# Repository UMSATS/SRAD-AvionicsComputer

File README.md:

# SRAD_V2

This repository contains the schematic, PCB, and supporting design files for the Student Researched and Designed (SRAD) rocket avionics computer.

## Project Structure

- **SRAD_V2.kicad_pro** — Main KiCad project file
- **SRAD_V2.kicad_sch** — Schematic file containing the full circuit design.
- **SRAD_V2.kicad_pcb** — PCB layout file for board routing and placement.
- **SRAD_V2-backups/** — Automatically generated backup files created by KiCad.
- **Custom E-cad Models/** — Custom or project-specific component symbols, footprints and 3D models used in the PCB design.

---

## System Overview

The schematic is organized into blocks for clarity:

- **Power Delivery System (PDS)**  
  Handles voltage regulation and distribution. Goal is to provide stable power to all avionics subsystems.

- **E-match Firing Circuit (EMFC)**  
  Provides quick burst of high current to e-matches via four separate channels. It also includes short circuit protection and various other safety features.

- **MCU (Microcontroller Unit)**  
  Central controller that interfaces with all sensors and peripherals. Will run the flight software and handle communication.

- **IMU for Sensing Motion and Temperature** -> LSM6DSV80XTR

- **Magnetometer** -> MMC5983MA

- **Barometer** -> MS5607-02BA

- **GPS** -> MAX-M10S

- **Data Storage** -> AT25SFQ64

---

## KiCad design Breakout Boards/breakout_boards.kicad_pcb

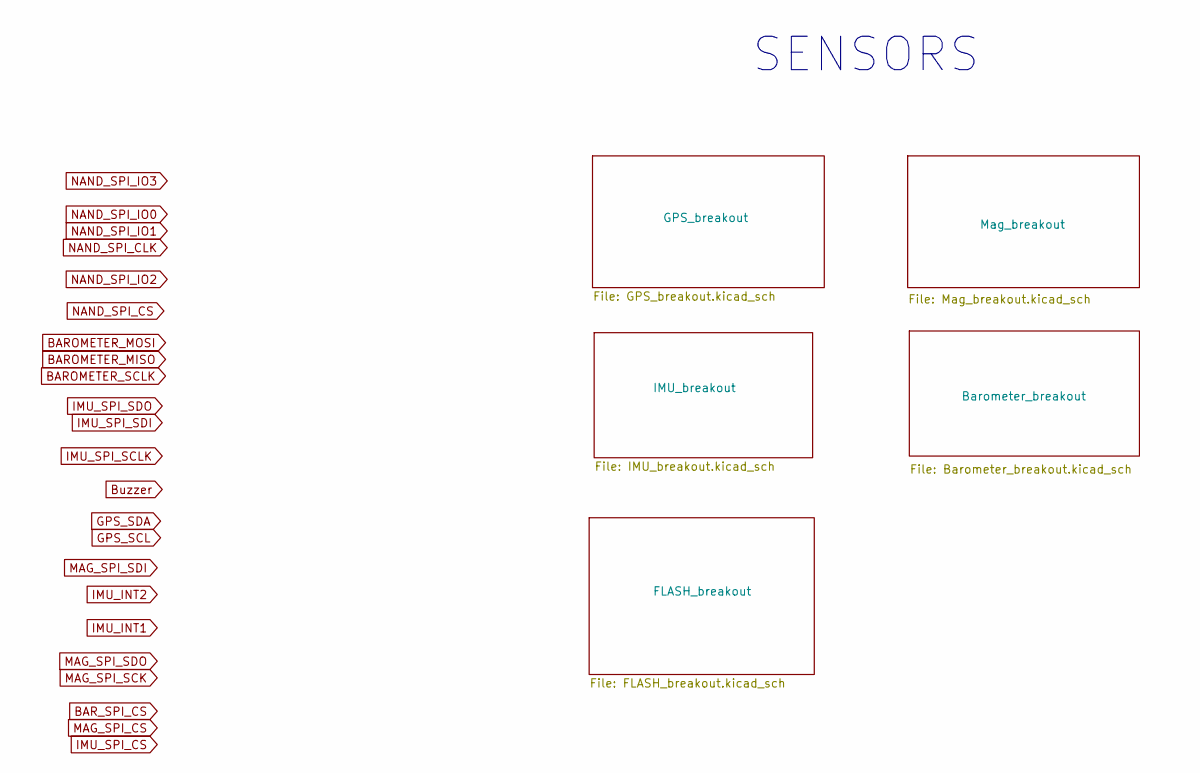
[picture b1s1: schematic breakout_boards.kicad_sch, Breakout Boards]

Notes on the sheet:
SENSORS

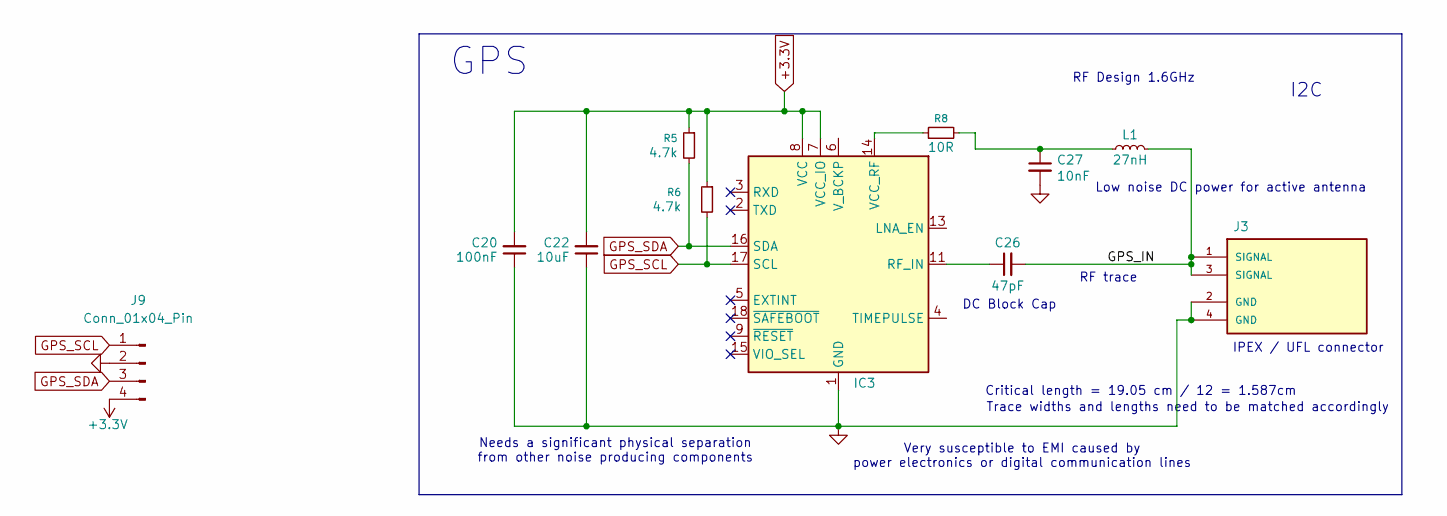
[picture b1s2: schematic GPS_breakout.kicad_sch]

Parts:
C20: 100nF; C_0603_1608Metric; Manufacturer_Part_Number C0603C104K5RAC3121
C22: 10uF; C_1206_3216Metric; Manufacturer_Part_Number CGA5L1X7R1E106K160DC
C26: 47pF; C_0402_1005Metric; Manufacturer_Part_Number C0402C470J3GACTU
C27: 10nF; C_0402_1005Metric; Manufacturer_Part_Number GRM155R71C103KA01D
IC3: ublox_MAX; Manufacturer_Part_Number MAX-M10S-00B
J3: SAMTEC_RSP-122811-02; Manufacturer_Part_Number RSP-122811-02
J9: Conn_01x04_Pin; PinHeader_1x04_P2.54mm_Vertical
L1: 27nH; L_0402_1005Metric; Manufacturer_Part_Number LQG15HS27NH02D
R5, R6: 4.7k; R_0603_1608Metric; Manufacturer_Part_Number CRCW06034K70FKEAHP
R8: 10R; R_1206_3216Metric; Manufacturer_Part_Number RC1206JR-7W10RL

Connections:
+3.3V: C20.2, C22.2, IC3.7 (VCC_IO), IC3.8 (VCC), J9.4, R5.1, R6.1; also elsewhere on the board
/GPS_breakout/GPS_IN: C26.2, J3.1 (SIGNAL), J3.3 (SIGNAL), L1.2
GND: C20.1, C22.1, C27.2, IC3.1 (GND), IC3.10 (GND), IC3.12 (GND), J3.2 (GND), J3.4 (GND), J9.2; also elsewhere on the board
GPS_SCL: IC3.17 (SCL), J9.1, R6.2
GPS_SDA: IC3.16 (SDA), J9.3, R5.2
unnamed: C27.1, L1.1, R8.2
unnamed: C26.1, IC3.11 (RF_IN)
unnamed: IC3.14 (VCC_RF), R8.1

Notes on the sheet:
Needs a significant physical separation from other noise producing components
Very susceptible to EMI caused by power electronics or digital communication lines
I2C
RF Design 1.6GHz
Critical length = 19.05 cm / 12 = 1.587cm
Trace widths and lengths need to be matched accordingly
IPEX / UFL connector
GPS
DC Block Cap
Low noise DC power for active antenna
RF trace

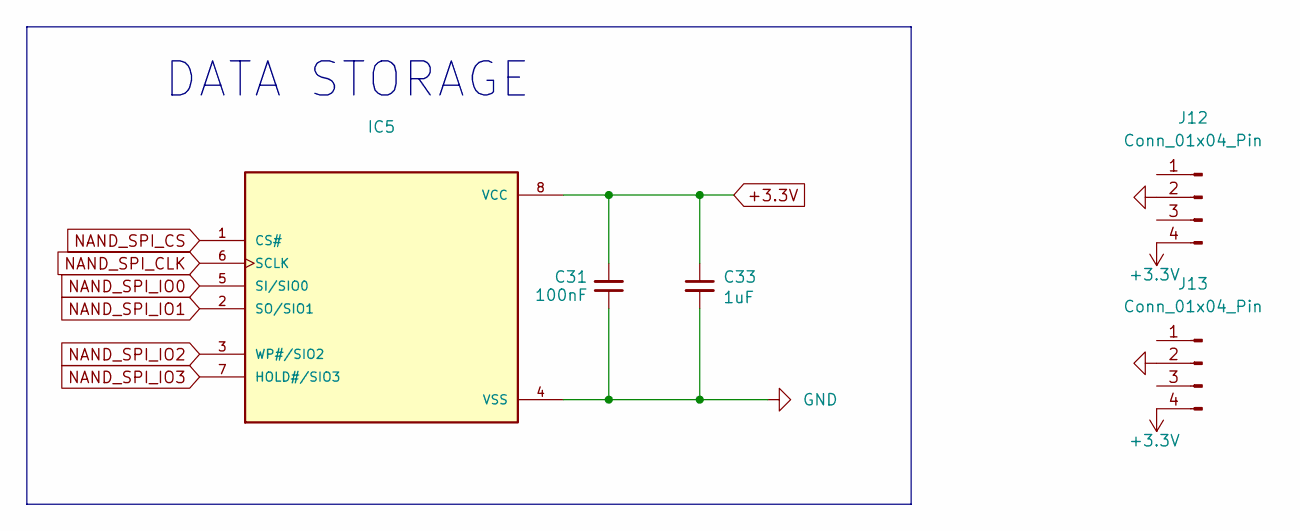
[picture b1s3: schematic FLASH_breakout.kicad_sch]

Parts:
C31: 100nF; C_0603_1608Metric; Manufacturer_Part_Number C0603C104K5RAC3121
C33: 1uF; C_0603_1608Metric; Manufacturer_Part_Number C0603C105K4RACTU
IC5: SON127P600X800X80-8N; PARTREV 1.0
J12, J13: Conn_01x04_Pin; PinHeader_1x04_P2.54mm_Vertical

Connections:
+3.3V: C31.2, C33.1, IC5.8 (VCC), J12.4, J13.4; also elsewhere on the board
GND: C31.1, C33.2, IC5.4 (VSS), J12.2, J13.2; also elsewhere on the board
NAND_SPI_CLK: IC5.6 (SCLK)
NAND_SPI_CS: IC5.1 (CS#)
NAND_SPI_IO0: IC5.5 (SI/SIO0)
NAND_SPI_IO1: IC5.2 (SO/SIO1)
NAND_SPI_IO2: IC5.3 (WP#/SIO2)
NAND_SPI_IO3: IC5.7 (HOLD#/SIO3)

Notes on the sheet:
DATA STORAGE

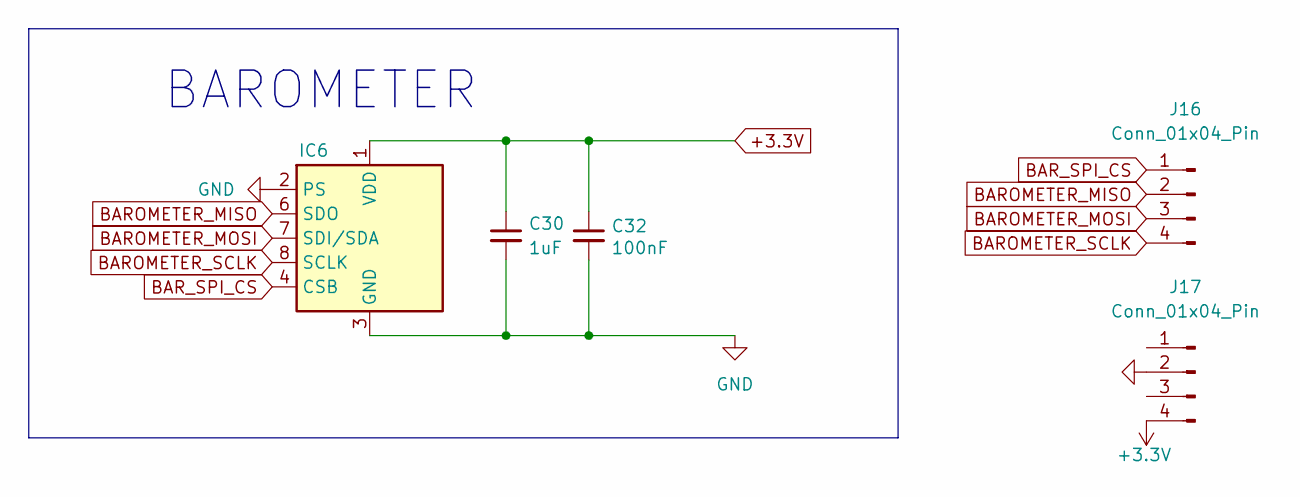
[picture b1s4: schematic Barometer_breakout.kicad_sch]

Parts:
C30: 1uF; C_0603_1608Metric; Manufacturer_Part_Number C0603C105K4RACTU
C32: 100nF; C_0603_1608Metric; Manufacturer_Part_Number C0603C104K5RAC3121
IC6: LGA-8_3x5mm_P1.25mm; Manufacturer_Part_Number MS560702BA03-50
J16, J17: Conn_01x04_Pin; PinHeader_1x04_P2.54mm_Vertical

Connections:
+3.3V: C30.1, C32.1, IC6.1 (VDD), J17.4; also elsewhere on the board
BAROMETER_MISO: IC6.6 (SDO), J16.2
BAROMETER_MOSI: IC6.7 (SDI/SDA), J16.3
BAROMETER_SCLK: IC6.8 (SCLK), J16.4
BAR_SPI_CS: IC6.4 (CSB), IC6.5 (CSB), J16.1
GND: C30.2, C32.2, IC6.2 (PS), IC6.3 (GND), J17.2; also elsewhere on the board

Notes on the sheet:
BAROMETER

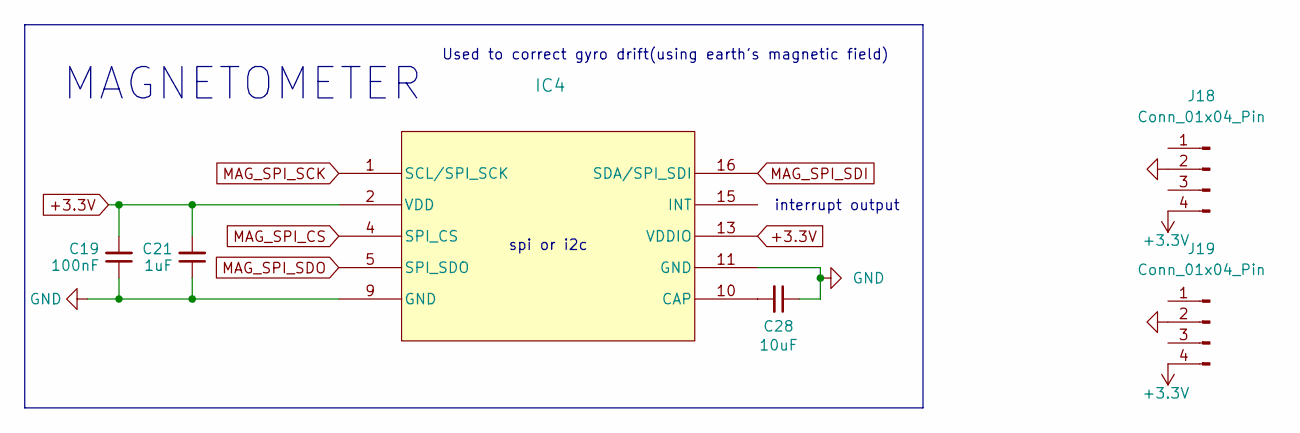
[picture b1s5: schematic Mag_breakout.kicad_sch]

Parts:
C19: 100nF; C_0603_1608Metric; Manufacturer_Part_Number C0603C104K5RAC3121
C21: 1uF; C_0603_1608Metric; Manufacturer_Part_Number C0603C105K4RACTU
C28: 10uF; C_1206_3216Metric; Manufacturer_Part_Number CGA5L1X7R1E106K160DC
IC4: MMC5983MA_MEM; Manufacturer_Part_Number MMC5983MA
J18, J19: Conn_01x04_Pin; PinHeader_1x04_P2.54mm_Vertical

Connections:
+3.3V: C19.2, C21.2, IC4.2 (VDD), IC4.13 (VDDIO), J18.4, J19.4; also elsewhere on the board
GND: C19.1, C21.1, C28.1, IC4.6 (NC), IC4.9 (GND), IC4.11 (GND), J18.2, J19.2; also elsewhere on the board
MAG_SPI_CS: IC4.3 (NC), IC4.4 (SPI_CS)
MAG_SPI_SCK: IC4.1 (SCL/SPI_SCK)
MAG_SPI_SDI: IC4.16 (SDA/SPI_SDI)
MAG_SPI_SDO: IC4.5 (SPI_SDO)
unnamed: C28.2, IC4.10 (CAP)

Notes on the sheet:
spi or i2c
interrupt output
MAGNETOMETER
Used to correct gyro drift(using earth's magnetic field)

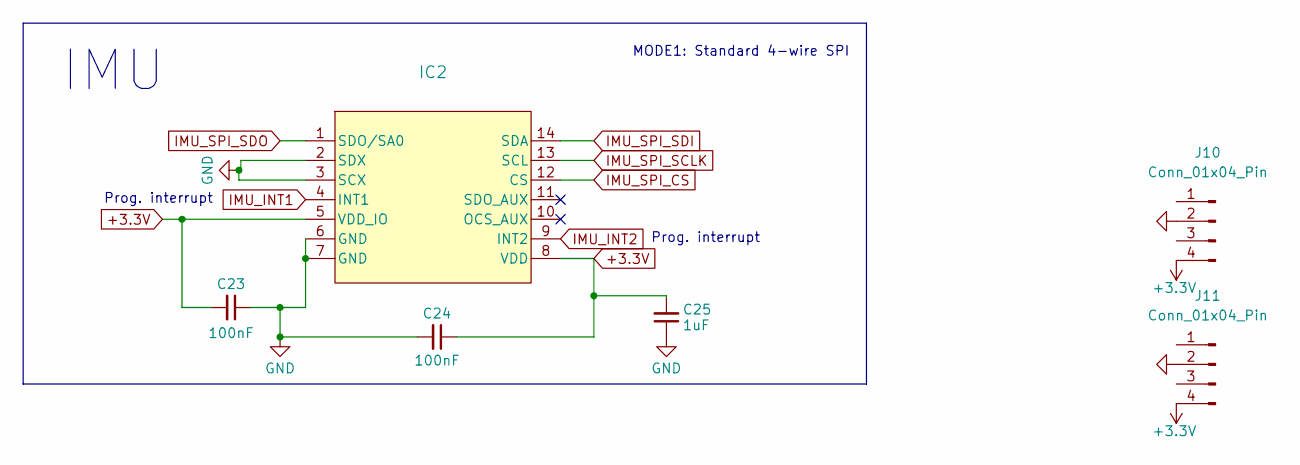
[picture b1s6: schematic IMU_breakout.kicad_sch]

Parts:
C23, C24: 100nF; C_0603_1608Metric; Manufacturer_Part_Number C0603C104K5RAC3121
C25: 1uF; C_0603_1608Metric; Manufacturer_Part_Number C0603C105K4RACTU
IC2: LGA14-L_2P59X3P1X0P5_STM; Manufacturer_Part_Number LSM6DSVTR
J10, J11: Conn_01x04_Pin; PinHeader_1x04_P2.54mm_Vertical

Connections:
+3.3V: C23.2, C24.1, C25.2, IC2.5 (VDD_IO), IC2.8 (VDD), J10.4, J11.4; also elsewhere on the board
GND: C23.1, C24.2, C25.1, IC2.2 (SDX), IC2.3 (SCX), IC2.6 (GND), IC2.7 (GND), J10.2, J11.2; also elsewhere on the board
IMU_INT1: IC2.4 (INT1)
IMU_INT2: IC2.9 (INT2)
IMU_SPI_CS: IC2.12 (CS)
IMU_SPI_SCLK: IC2.13 (SCL)
IMU_SPI_SDI: IC2.14 (SDA)
IMU_SPI_SDO: IC2.1 (SDO/SA0)

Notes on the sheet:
Prog. interrupt
IMU
MODE1: Standard 4-wire SPI

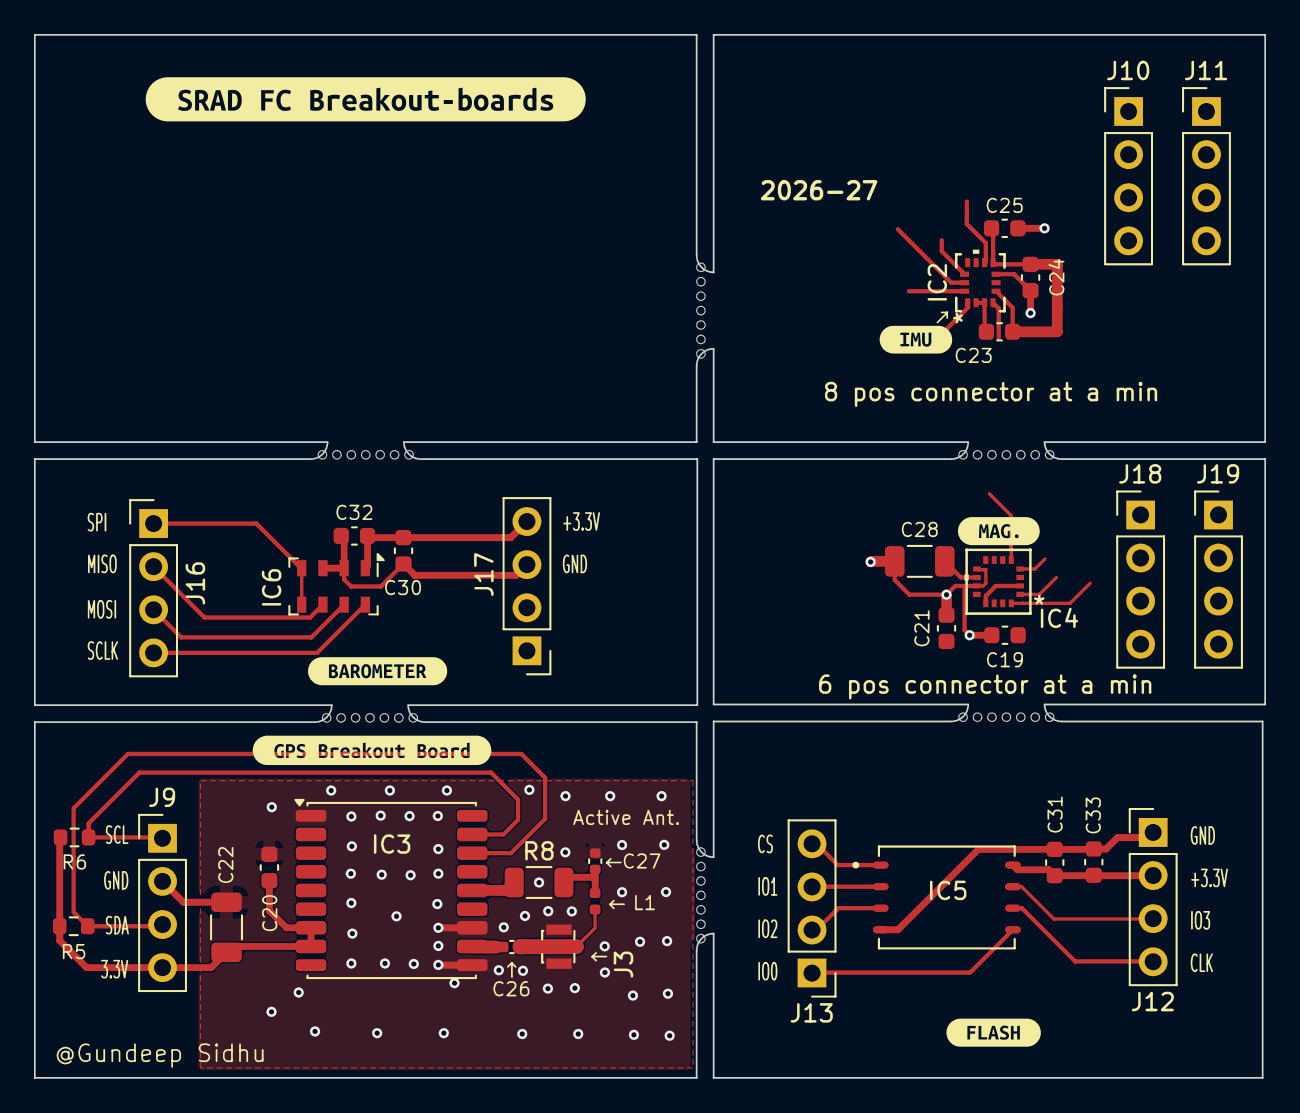
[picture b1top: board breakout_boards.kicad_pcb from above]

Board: 2 copper layers, 72.5 x 61.5 mm, 39 parts (0 on the bottom side), 13 nets.

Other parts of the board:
kibuzzard-6A6394C9: G***; kibuzzard-6A6394C9
kibuzzard-6A6394D1: G***; kibuzzard-6A6394D1
kibuzzard-6A876244: G***; kibuzzard-6A876244
kibuzzard-6A982418: G***; kibuzzard-6A982418
kibuzzard-6AAC4875: G***; kibuzzard-6AAC4875
kibuzzard-6AB434CE: G***; kibuzzard-6AB434CE

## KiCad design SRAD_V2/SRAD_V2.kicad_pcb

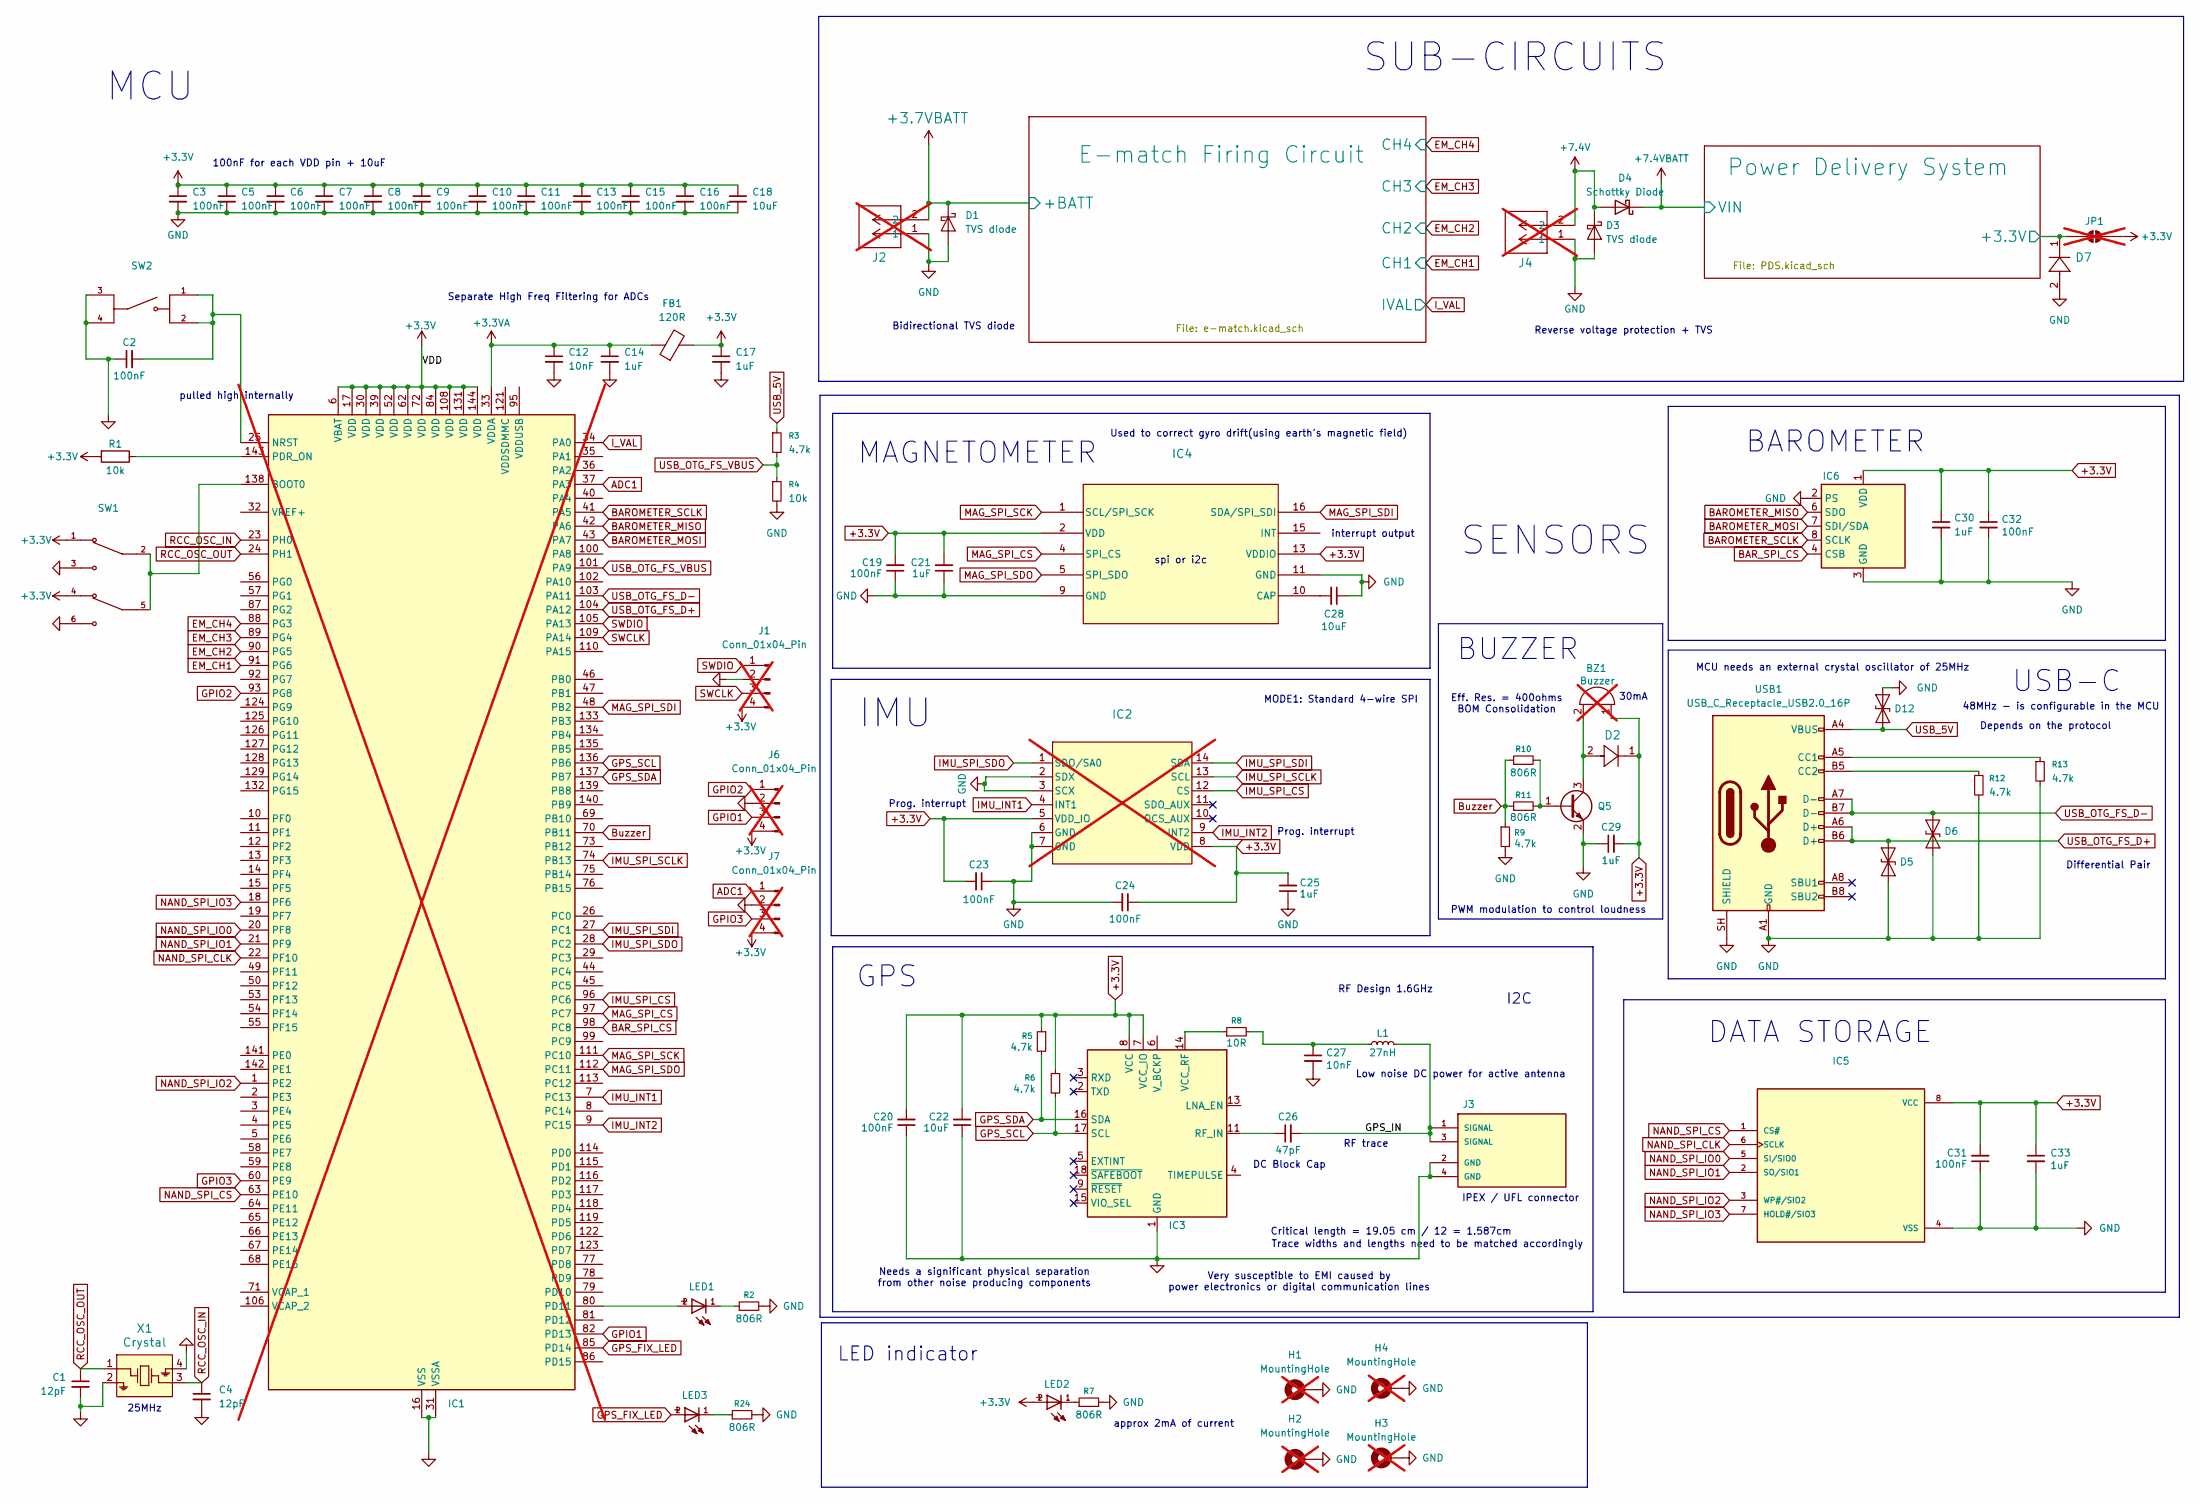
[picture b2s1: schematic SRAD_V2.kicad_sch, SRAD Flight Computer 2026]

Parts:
BZ1: Buzzer; Buzzer_12x9.5RM7.6; Manufacturer_Part_Number CI12E-05T230-C-6; not fitted
C1, C4: 12pF; C_0402_1005Metric; Manufacturer_Part_Number GRM1555C1H120FA01J
C2, C3, C5, C6, C7, C8, C9, C10, C11, C13, C15, C16, C19, C20, C23, C24, C31, C32: 100nF; C_0603_1608Metric; Manufacturer_Part_Number C0603C104K5RAC3121
C12, C27: 10nF; C_0402_1005Metric; Manufacturer_Part_Number GRM155R71C103KA01D
C14, C17, C21, C25, C29, C30, C33: 1uF; C_0603_1608Metric; Manufacturer_Part_Number C0603C105K4RACTU
C18, C22, C28: 10uF; C_1206_3216Metric; Manufacturer_Part_Number CGA5L1X7R1E106K160DC
C26: 47pF; C_0402_1005Metric; Manufacturer_Part_Number C0402C470J3GACTU
D1, D3: TVS diode; D_SOD-123F; Manufacturer_Part_Number SMF10CA
D2: DIODE_MSP3V3; Manufacturer_Part_Number MSS1P5-M3/89A
D4: Schottky Diode; D_SMA; Manufacturer_Part_Number MBRA340T3G
D5, D6, D12: TVS diode; D_SOD-323; Manufacturer_Part_Number STS321050B100
D7: TVS diode; CR_PTVS3V_NEX-L; Manufacturer_Part_Number PTVS3V3S1UTR,115
FB1: 120R; L_0603_1608Metric; Manufacturer_Part_Number MH1608-121Y
H1, H2, H3, H4: MountingHole; MountingHole_3.5mm_Pad_Via; not fitted
IC1: LQFP-144_20x20mm_P0.5mm; Manufacturer_Part_Number STM32F767ZIT6; not fitted
IC2: LGA14-L_2P59X3P1X0P5_STM; Manufacturer_Part_Number LSM6DSVTR; not fitted
IC3: ublox_MAX; Manufacturer_Part_Number MAX-M10S-00B
IC4: MMC5983MA_MEM; Manufacturer_Part_Number MMC5983MA
IC5: SON127P600X800X80-8N; PARTREV 1.0
IC6: LGA-8_3x5mm_P1.25mm; Manufacturer_Part_Number MS560702BA03-50
J1, J6, J7: Conn_01x04_Pin; PinHeader_1x04_P2.54mm_Vertical; not fitted
J2, J4: CONN2_S02B-XASS_295x496_JST; Manufacturer_Part_Number S02B-XASS-1; not fitted
J3: SAMTEC_RSP-122811-02; Manufacturer_Part_Number RSP-122811-02
JP1: SolderJumper_2_Open; SolderJumper-2_P1.3mm_Open_RoundedPad1.0x1.5mm; not fitted
L1: 27nH; L_0402_1005Metric; Manufacturer_Part_Number LQG15HS27NH02D
LED1, LED2, LED3: LED; WL-SMCW_1206; Manufacturer_Part_Number 150120SS75000
Q5: NPN BJT; SOT-23; Manufacturer_Part_Number MMBT3904LT3G
R1, R4: 10k; R_0603_1608Metric; Manufacturer_Part_Number CRT0603-BY-1002ELF
R2, R7, R10, R11, R24: 806R; R_0603_1608Metric; Manufacturer_Part_Number RT0603BRD07806RL
R3, R5, R6, R9, R12, R13: 4.7k; R_0603_1608Metric; Manufacturer_Part_Number CRCW06034K70FKEAHP
R8: 10R; R_1206_3216Metric; Manufacturer_Part_Number RC1206JR-7W10RL
SW1: SW_SLW-913535-2A-SMT; PARTREV 1.01
SW2: SW_TS18-5-15-SL-160-SMT-TR; PARTREV 1.02
USB1: USB_C_Receptacle_USB2.0_16P; USB_C_Receptacle_GCT_USB4105-xx-A_16P_TopMnt_Horizontal; Manufacturer_Part_Number USB4105-GF-A
X1: Crystal; VXM7_MCH; Manufacturer_Part_Number VXM7-9032-25M0000000

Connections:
+3.3V: BZ1.1 (+), C3.1, C5.1, C6.1, C7.1, C8.1, C9.1, C10.1, C11.1, C13.1, C15.1, C16.1, C17.1, C18.1, C19.2, C20.2, C21.2, C22.2, C23.2, C24.1, C25.2, C29.2, C30.1, C31.2, C32.1, C33.1, D2.1, FB1.2, IC1.6 (VBAT), IC1.17 (VDD), IC1.30 (VDD), IC1.39 (VDD), IC1.52 (VDD), IC1.62 (VDD), IC1.72 (VDD), IC1.84 (VDD), IC1.108 (VDD), IC1.131 (VDD), IC1.144 (VDD), IC2.5 (VDD_IO), IC2.8 (VDD), IC3.7 (VCC_IO), IC3.8 (VCC), IC4.2 (VDD), IC4.13 (VDDIO), IC5.8 (VCC), IC6.1 (VDD), J1.4, J6.4, J7.4, JP1.2 (B), LED2.2, R1.2, R5.1, R6.1, SW1.1, SW1.4; also elsewhere on the board
+3.3VA: C12.1, C14.1, FB1.1, IC1.33 (VDDA)
+3.7VBATT: D1.1 (K), J2.2; also elsewhere on the board
+7.4V: D3.1 (K), D4.2 (A), J4.2; also elsewhere on the board
+7.4VBATT: D4.1 (K); also elsewhere on the board
/GPS_IN: C26.2, J3.1 (SIGNAL), J3.3 (SIGNAL), L1.2
/Power Delivery System/+3.3V: D7.1, JP1.1 (A); also elsewhere on the board
ADC1: IC1.37 (PA3), J7.1
BAROMETER_MISO: IC1.42 (PA6), IC6.6 (SDO)
BAROMETER_MOSI: IC1.43 (PA7), IC6.7 (SDI/SDA)
BAROMETER_SCLK: IC1.41 (PA5), IC6.8 (SCLK)
BAR_SPI_CS: IC1.98 (PC8), IC6.4 (CSB), IC6.5 (CSB)
Buzzer: IC1.70 (PB11), R9.1, R10.1, R11.1
EM_CH1: IC1.91 (PG6); also elsewhere on the board
EM_CH2: IC1.90 (PG5); also elsewhere on the board
EM_CH3: IC1.89 (PG4); also elsewhere on the board
EM_CH4: IC1.88 (PG3); also elsewhere on the board
GND: C1.2, C2.1, C3.2, C4.2, C5.2, C6.2, C7.2, C8.2, C9.2, C10.2, C11.2, C12.2, C13.2, C14.2, C15.2, C16.2, C17.2, C18.2, C19.1, C20.1, C21.1, C22.1, C23.1, C24.2, C25.1, C27.2, C28.1, C29.1, C30.2, C31.1, C32.2, C33.2, D1.2 (A), D3.2 (A), D5.1 (A1), D6.1 (A1), D7.2, D12.2 (A2), H1.1 (1_1), H2.1 (1_1), H3.1 (1_1), H4.1 (1_1), IC1.16 (VSS), IC1.31 (VSSA), IC1.38 (VSS), IC1.51 (VSS), IC1.61 (VSS), IC1.83 (VSS), IC1.94 (VSS), IC1.107 (VSS), IC1.120 (VSS), IC1.130 (VSS), IC2.2 (SDX), IC2.3 (SCX), IC2.6 (GND), IC2.7 (GND), IC3.1 (GND), IC3.10 (GND), IC3.12 (GND), IC4.6 (NC), IC4.9 (GND), IC4.11 (GND), IC5.4 (VSS), IC6.2 (PS), IC6.3 (GND), J1.2, J2.1, J3.2 (GND), J3.4 (GND), J4.1, J6.2, J7.2, Q5.2 (E), R2.2, R4.2, R7.2, R9.2, R12.2, R13.2, R24.2, SW1.3, SW1.6, SW2.3, SW2.4, USB1.A1 (GND), USB1.A12 (GND), USB1.B1 (GND), USB1.B12 (GND), USB1.SH (SHIELD), X1.2, X1.4; also elsewhere on the board
GPIO1: IC1.82 (PD13), J6.3
GPIO2: IC1.93 (PG8), J6.1
GPIO3: IC1.60 (PE9), J7.3
GPS_FIX_LED: IC1.85 (PD14), LED3.2
GPS_SCL: IC1.136 (PB6), IC3.17 (SCL), R6.2
GPS_SDA: IC1.137 (PB7), IC3.16 (SDA), R5.2
IMU_INT1: IC1.7 (PC13), IC2.4 (INT1)
IMU_INT2: IC1.9 (PC15), IC2.9 (INT2)
IMU_SPI_CS: IC1.96 (PC6), IC2.12 (CS)
IMU_SPI_SCLK: IC1.74 (PB13), IC2.13 (SCL)
IMU_SPI_SDI: IC1.27 (PC1), IC2.14 (SDA)
IMU_SPI_SDO: IC1.28 (PC2), IC2.1 (SDO/SA0)
I_VAL: IC1.34 (PA0); also elsewhere on the board
MAG_SPI_CS: IC1.97 (PC7), IC4.3 (NC), IC4.4 (SPI_CS)
MAG_SPI_SCK: IC1.111 (PC10), IC4.1 (SCL/SPI_SCK)
MAG_SPI_SDI: IC1.48 (PB2), IC4.16 (SDA/SPI_SDI)
MAG_SPI_SDO: IC1.112 (PC11), IC4.5 (SPI_SDO)
NAND_SPI_CLK: IC1.22 (PF10), IC5.6 (SCLK)
NAND_SPI_CS: IC1.63 (PE10), IC5.1 (CS#)
NAND_SPI_IO0: IC1.20 (PF8), IC5.5 (SI/SIO0)
NAND_SPI_IO1: IC1.21 (PF9), IC5.2 (SO/SIO1)
NAND_SPI_IO2: IC1.1 (PE2), IC5.3 (WP#/SIO2)
NAND_SPI_IO3: IC1.18 (PF6), IC5.7 (HOLD#/SIO3)
unnamed: BZ1.2 (-), D2.2, Q5.3 (C)
unnamed: C27.1, L1.1, R8.2
unnamed: IC1.138 (BOOT0), SW1.2, SW1.5
unnamed: C2.2, IC1.25 (NRST), SW2.1, SW2.2
unnamed: IC1.80 (PD11), LED1.2
unnamed: IC1.143 (PDR_ON), R1.1
unnamed: C26.1, IC3.11 (RF_IN)
unnamed: IC3.14 (VCC_RF), R8.1
unnamed: C28.2, IC4.10 (CAP)
unnamed: LED1.1, R2.1
unnamed: LED2.1, R7.1
unnamed: LED3.1, R24.1
unnamed: Q5.1 (B), R10.2, R11.2
unnamed: R13.1, USB1.A5 (CC1)
unnamed: R12.1, USB1.B5 (CC2)
RCC_OSC_IN: C4.1, IC1.23 (PH0), X1.3
RCC_OSC_OUT: C1.1, IC1.24 (PH1), X1.1
SWCLK: IC1.109 (PA14), J1.3
SWDIO: IC1.105 (PA13), J1.1
USB_5V: D12.1 (A1), R3.1, USB1.A4 (VBUS), USB1.A9 (VBUS), USB1.B4 (VBUS), USB1.B9 (VBUS)
USB_OTG_FS_D+: D5.2 (A2), IC1.104 (PA12), USB1.A6 (D+), USB1.B6 (D+)
USB_OTG_FS_D-: D6.2 (A2), IC1.103 (PA11), USB1.A7 (D-), USB1.B7 (D-)
USB_OTG_FS_VBUS: IC1.101 (PA9), R3.2, R4.1

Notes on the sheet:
48MHz - is configurable in the MCU
DATA STORAGE
Trace widths and lengths need to be matched accordingly
Reverse voltage protection + TVS
Differential Pair
RF trace
25MHz
MODE1: Standard 4-wire SPI
Very susceptible to EMI caused by power electronics or digital communication lines
MAGNETOMETER
BUZZER
Critical length = 19.05 cm / 12 = 1.587cm
SENSORS
Depends on the protocol
30mA
RF Design 1.6GHz
pulled high internally
Prog. interrupt
Eff. Res. = 400ohms BOM Consolidation
Bidirectional TVS diode
LED indicator
Needs a significant physical separation from other noise producing components
MCU
Used to correct gyro drift(using earth's magnetic field)
I2C
approx 2mA of current
USB-C
spi or i2c
DC Block Cap
IMU
100nF for each VDD pin + 10uF
GPS
PWM modulation to control loudness
interrupt output
SUB-CIRCUITS
MCU needs an external crystal oscillator of 25MHz
IPEX / UFL connector
Separate High Freq Filtering for ADCs
Low noise DC power for active antenna
BAROMETER

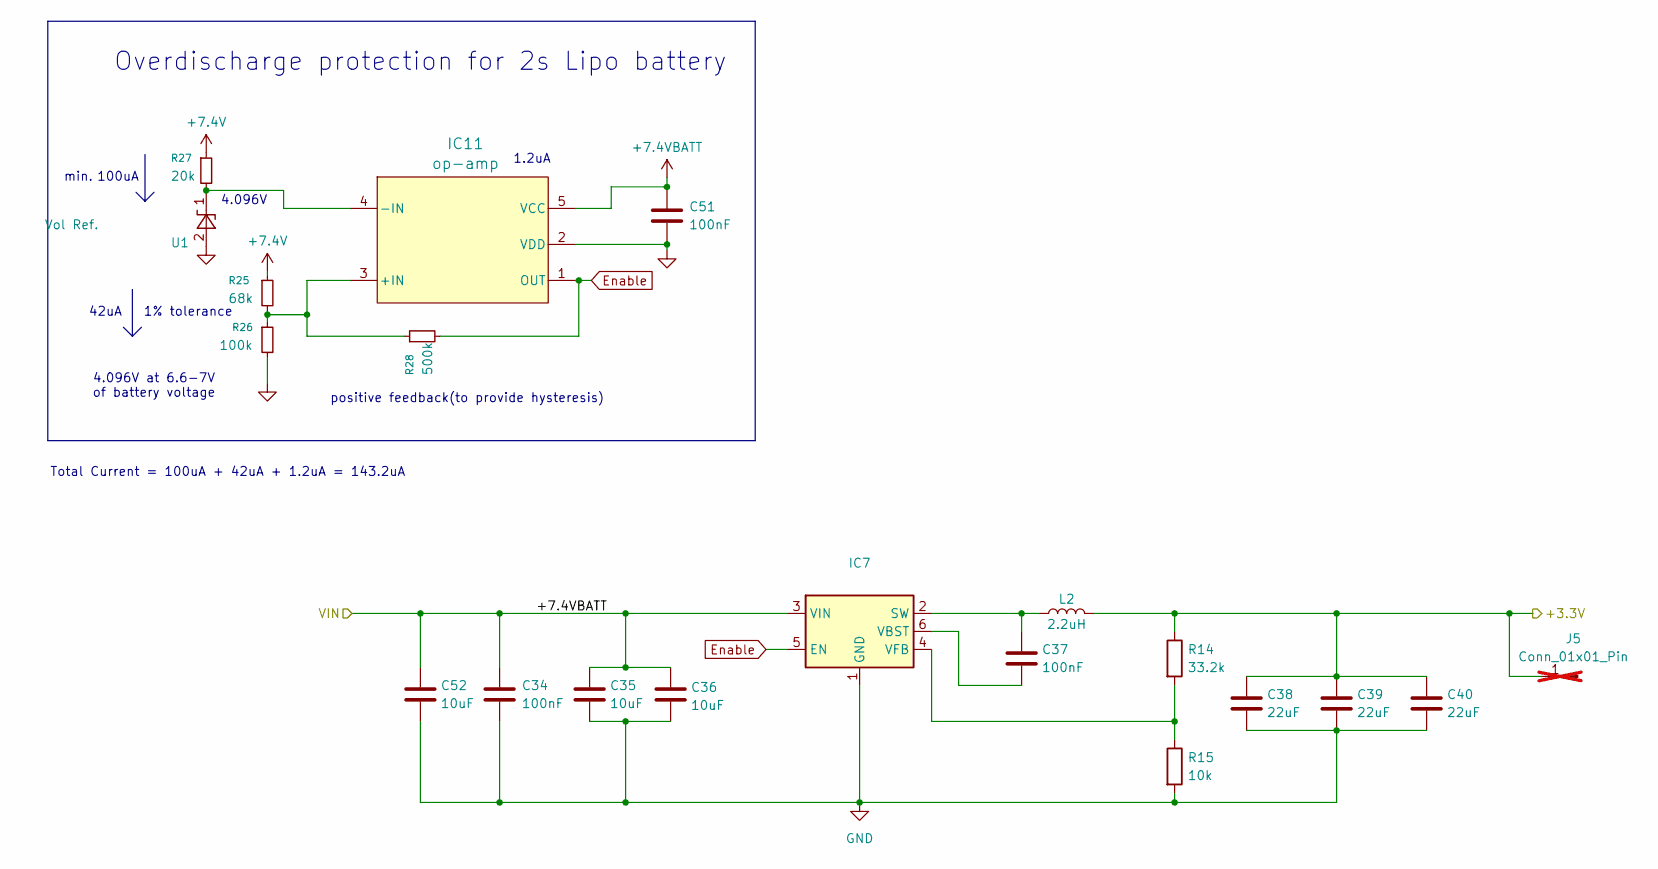
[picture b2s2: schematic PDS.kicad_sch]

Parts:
C34, C37, C51: 100nF; C_0603_1608Metric; Manufacturer_Part_Number C0603C104K5RAC3121
C35, C36, C52: 10uF; C_1206_3216Metric; Manufacturer_Part_Number CGA5L1X7R1E106K160DC
C38, C39, C40: 22uF; C_1206_3216Metric; Manufacturer_Part_Number GRM31CC81E226ME11L
IC7: SOT-23-6; Manufacturer_Part_Number TPS563200DDCT
IC11: op-amp; SOT23-5L_STM; Manufacturer_Part_Number TS941ILT
J5: Conn_01x01_Pin; PinHeader_1x01_P1.27mm_Vertical; not fitted
L2: 2.2uH; L_Bourns_SRP5030T; Manufacturer_Part_Number SRP5030TA-2R2M
R14: 33.2k; R_0603_1608Metric; Manufacturer_Part_Number CRCW060333K2FKTA
R15: 10k; R_0603_1608Metric; Manufacturer_Part_Number CRT0603-BY-1002ELF
R25: 68k; R_0603_1608Metric; Manufacturer_Part_Number CRG0603F68K
R26: 100k; R_0603_1608Metric; Manufacturer_Part_Number RT0603FRD07100KL
R27: 20k; R_0603_1608Metric; Manufacturer_Part_Number RMCF0603JT20K0
R28: 500k; R_0603_1608Metric; Manufacturer_Part_Number RT0603FRE07510KL
U1: Vol Ref.; SOT-23; MPN LM4040CYM3-4.1-TR

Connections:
+7.4V: R25.1, R27.1; also elsewhere on the board
+7.4VBATT: C34.1, C35.1, C36.1, C51.1, C52.1, IC7.3 (VIN), IC11.5 (VCC); also elsewhere on the board
/Power Delivery System/+3.3V: C38.1, C39.1, C40.1, J5.1 (Pin_1_1), L2.2, R14.1; also elsewhere on the board
Enable: IC7.5 (EN), IC11.1 (OUT), R28.2
GND: C34.2, C35.2, C36.2, C38.2, C39.2, C40.2, C51.2, C52.2, IC7.1 (GND), IC11.2 (VDD), R15.2, R26.2, U1.2 (A); also elsewhere on the board
unnamed: C37.1, IC7.2 (SW), L2.1
unnamed: C37.2, IC7.6 (VBST)
unnamed: IC7.4 (VFB), R14.2, R15.1
unnamed: IC11.3 (+IN), R25.2, R26.1, R28.1
unnamed: IC11.4 (-IN), R27.2, U1.1 (K)

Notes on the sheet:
4.096V at 6.6-7V of battery voltage
100uA
Overdischarge protection for 2s Lipo battery
1% tolerance
Total Current = 100uA + 42uA + 1.2uA = 143.2uA
positive feedback(to provide hysteresis)
42uA
min.
1.2uA
4.096V

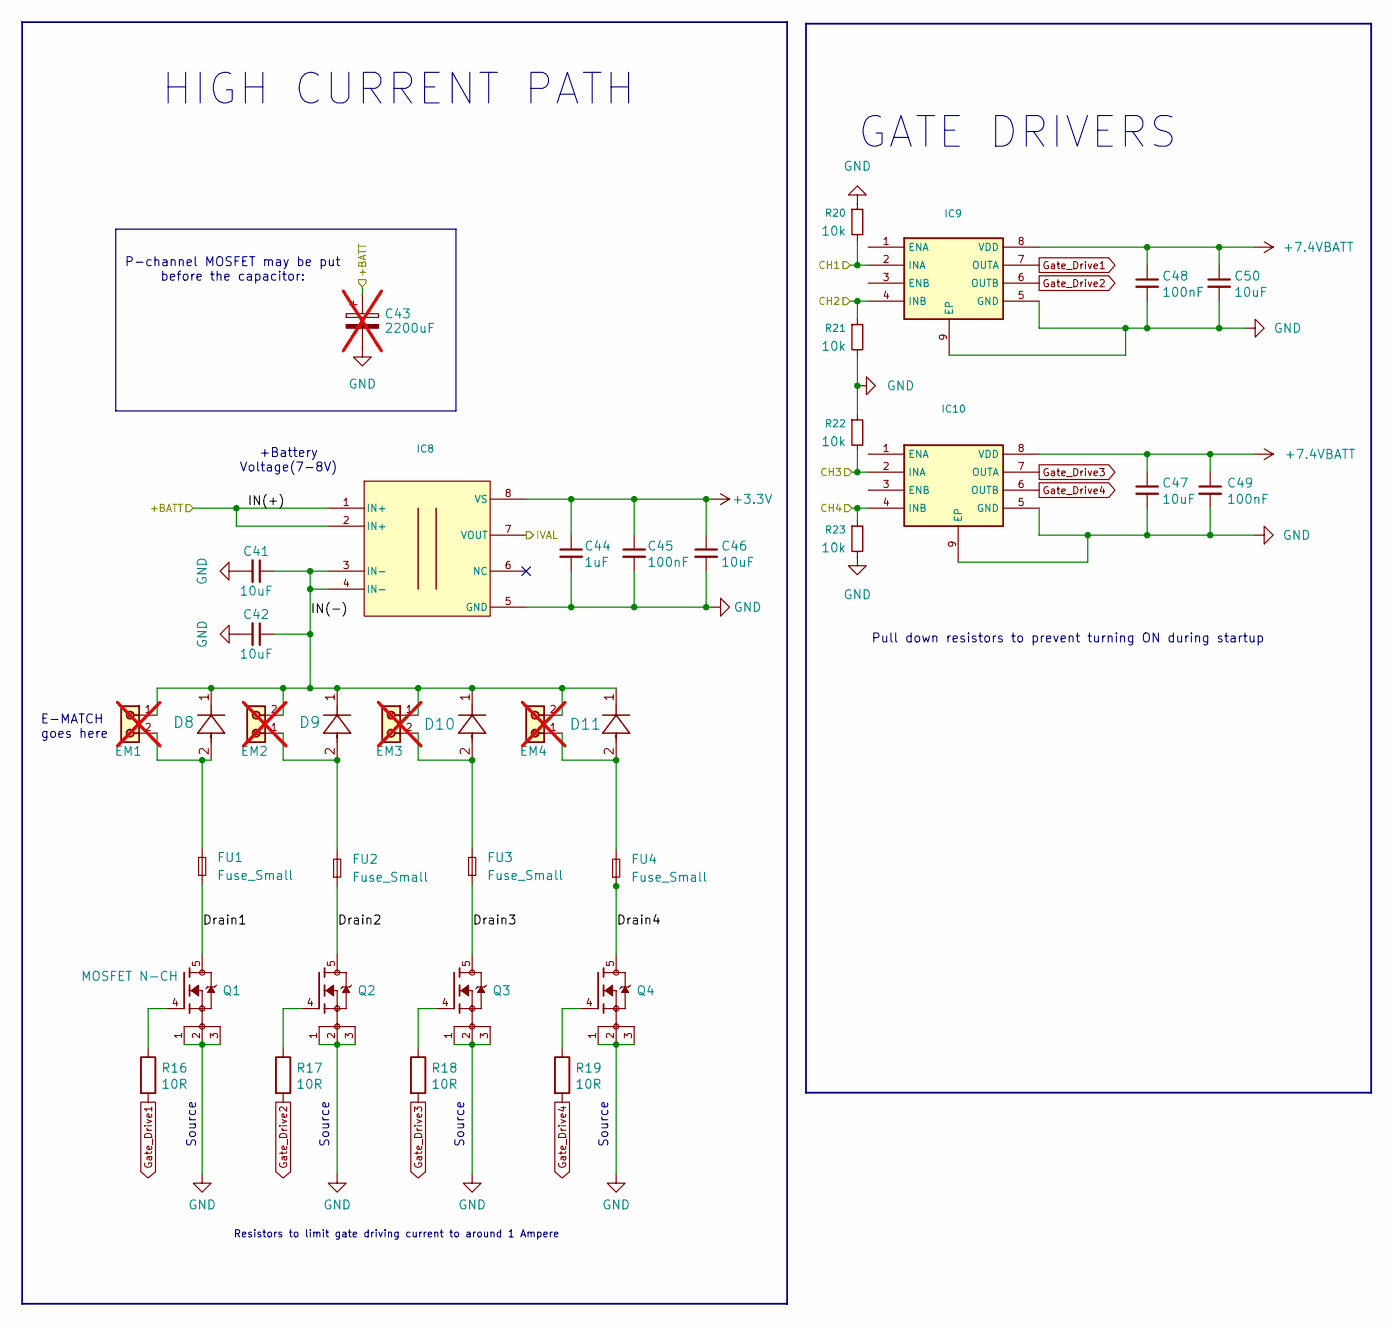
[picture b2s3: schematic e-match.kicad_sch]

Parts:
C41, C42, C46, C47, C50: 10uF; C_1206_3216Metric; Manufacturer_Part_Number CGA5L1X7R1E106K160DC
C43: 2200uF; CP_Radial_D10.0mm_P5.00mm; Manufacturer_Part_Number A750MW228M1CAAE010; not fitted
C44: 1uF; C_0603_1608Metric; Manufacturer_Part_Number C0603C105K4RACTU
C45, C48, C49: 100nF; C_0603_1608Metric; Manufacturer_Part_Number C0603C104K5RAC3121
D8, D9, D10, D11: DIODE_MSP3V3; Manufacturer_Part_Number MSS1P5-M3/89A
EM1, EM2, EM3, EM4: 691210910002; Manufacturer_Part_Number 691210910002; DigiKey_Part_Number 732-691210910002-ND; not fitted
FU1, FU2, FU3, FU4: Fuse_Small; Fuse_1206_3216Metric_Pad1.42x1.75mm_HandSolder; Manufacturer_Part_Number SF-1206SP500M-2
IC8: D0008A-IPC_A; Manufacturer_Part_Number TMCS1108A2UQDR
IC9, IC10: SOP65P490X110-9N; Manufacturer_Part_Number NCV81071BZR2G
Q1, Q2, Q3, Q4: MOSFET N-CH; TRANS_NTMFS5C673NT1G; PARTREV 0
R16, R17, R18, R19: 10R; R_1206_3216Metric; Manufacturer_Part_Number RC1206JR-7W10RL
R20, R21, R22, R23: 10k; R_0603_1608Metric; Manufacturer_Part_Number CRT0603-BY-1002ELF

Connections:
+3.3V: C44.1, C45.1, C46.1, IC8.8 (VS); also elsewhere on the board
+3.7VBATT: C43.1, IC8.1 (IN+), IC8.2 (IN+); also elsewhere on the board
+7.4VBATT: C47.1, C48.1, C49.1, C50.1, IC9.8 (VDD), IC10.8 (VDD); also elsewhere on the board
/E-match Firing Circuit/Drain1: FU1.1, Q1.5
/E-match Firing Circuit/Drain2: FU2.1, Q2.5
/E-match Firing Circuit/Drain3: FU3.1, Q3.5
/E-match Firing Circuit/Drain4: FU4.1, Q4.5
/E-match Firing Circuit/IN(-): C41.1, C42.1, D8.1, D9.1, D10.1, D11.1, EM1.1, EM2.2, EM3.1, EM4.2, IC8.3 (IN-), IC8.4 (IN-)
EM_CH1: IC9.2 (INA), R20.2; also elsewhere on the board
EM_CH2: IC9.4 (INB), R21.1; also elsewhere on the board
EM_CH3: IC10.2 (INA), R22.2; also elsewhere on the board
EM_CH4: IC10.4 (INB), R23.1; also elsewhere on the board
GND: C41.2, C42.2, C43.2, C44.2, C45.2, C46.2, C47.2, C48.2, C49.2, C50.2, IC8.5 (GND), IC9.5 (GND), IC9.9 (EP), IC10.5 (GND), IC10.9 (EP), Q1.1, Q1.2, Q1.3, Q2.1, Q2.2, Q2.3, Q3.1, Q3.2, Q3.3, Q4.1, Q4.2, Q4.3, R20.1, R21.2, R22.1, R23.2; also elsewhere on the board
Gate_Drive1: IC9.7 (OUTA), R16.2
Gate_Drive2: IC9.6 (OUTB), R17.2
Gate_Drive3: IC10.7 (OUTA), R18.2
Gate_Drive4: IC10.6 (OUTB), R19.2
I_VAL: IC8.7 (VOUT); also elsewhere on the board
unnamed: D8.2, EM1.2, FU1.2
unnamed: D9.2, EM2.1, FU2.2
unnamed: D10.2, EM3.2, FU3.2
unnamed: D11.2, EM4.1, FU4.2
unnamed: Q1.4, R16.1
unnamed: Q2.4, R17.1
unnamed: Q3.4, R18.1
unnamed: Q4.4, R19.1

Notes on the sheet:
Source
+Battery Voltage(7-8V)
Resistors to limit gate driving current to around 1 Ampere
E-MATCH goes here
HIGH CURRENT PATH
GATE DRIVERS
P-channel MOSFET may be put before the capacitor:
Pull down resistors to prevent turning ON during startup
